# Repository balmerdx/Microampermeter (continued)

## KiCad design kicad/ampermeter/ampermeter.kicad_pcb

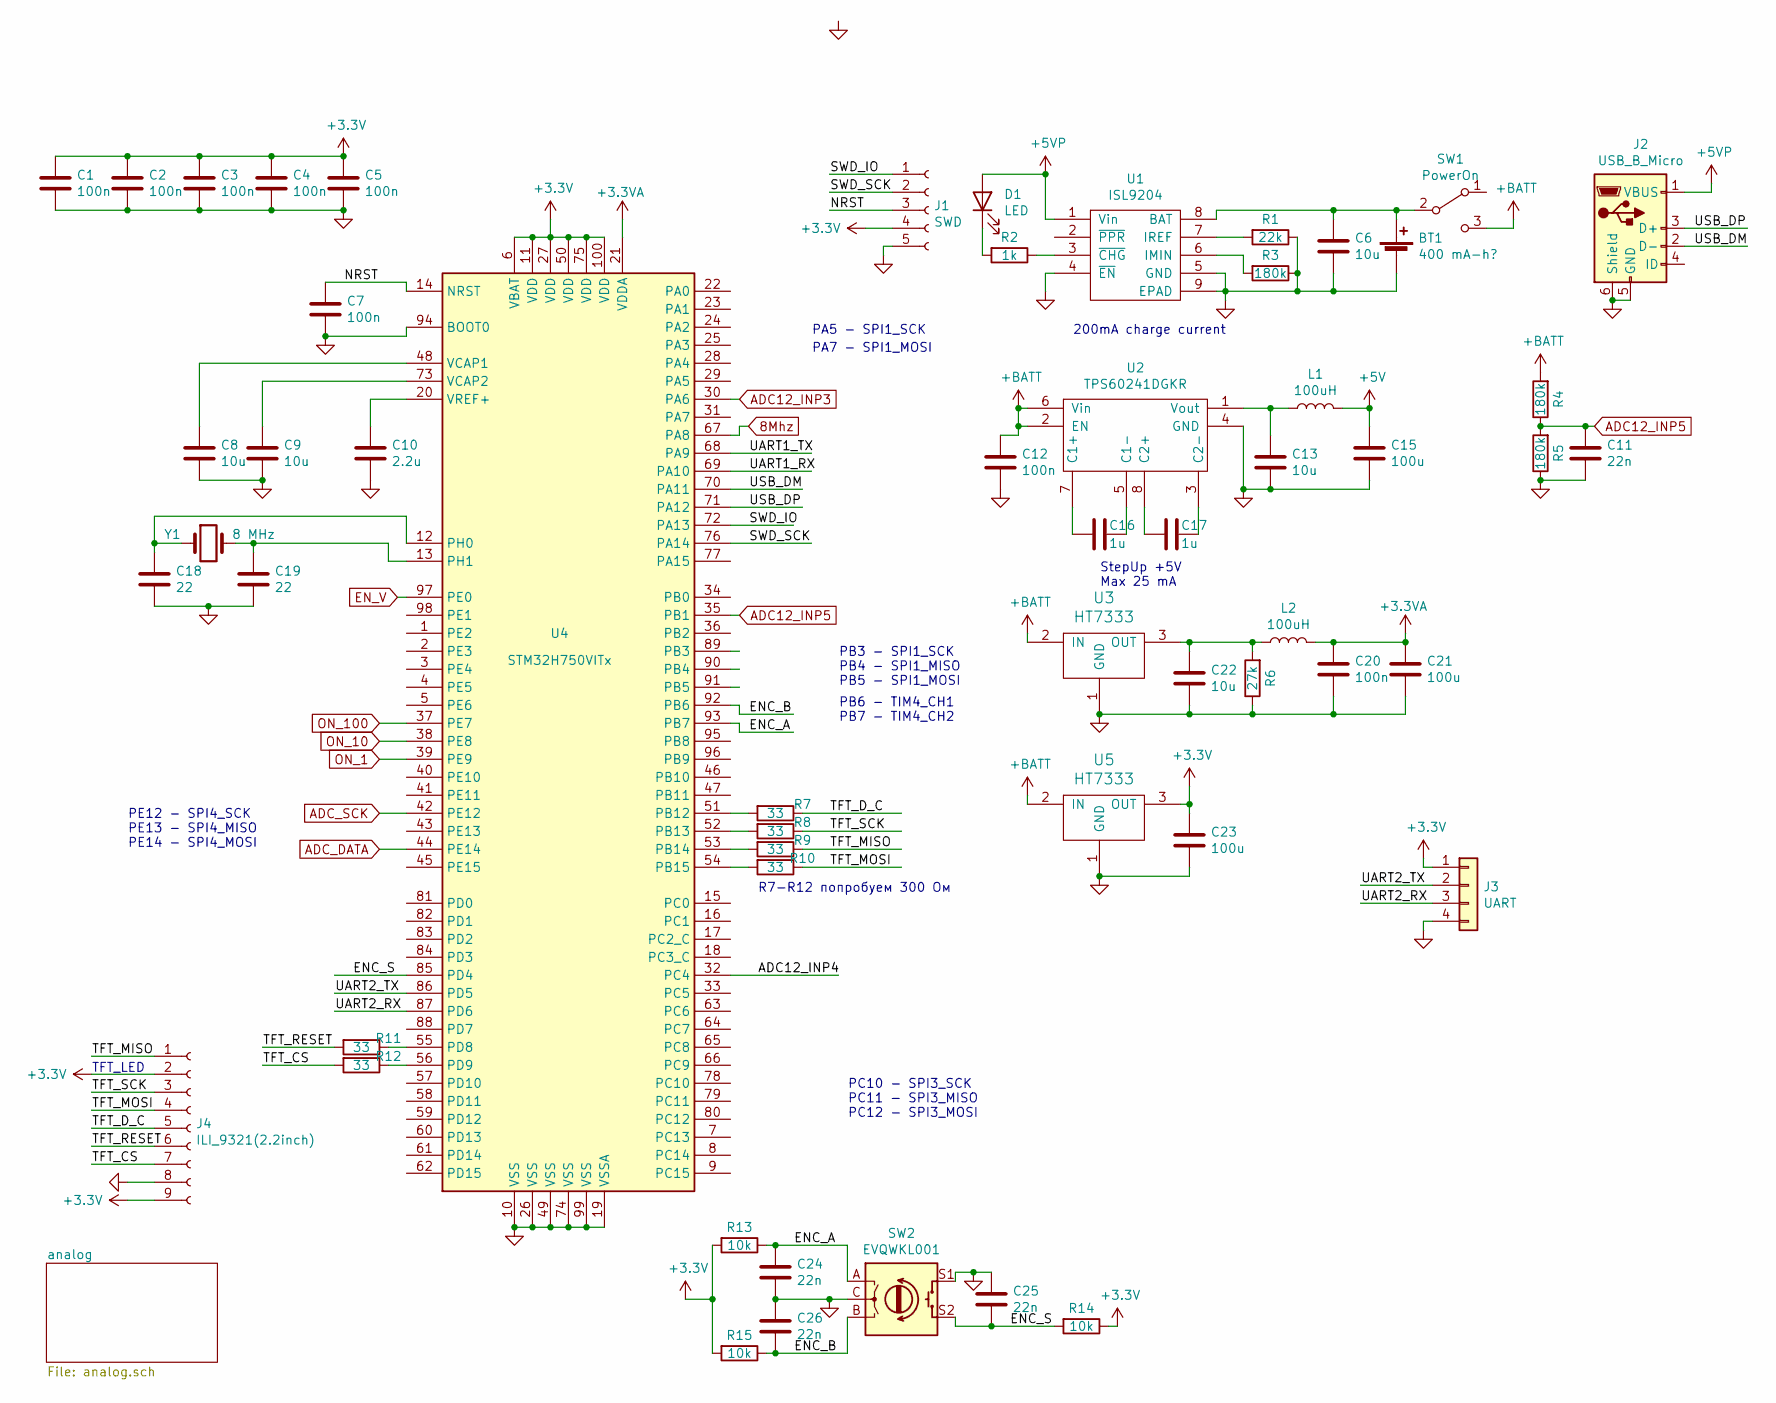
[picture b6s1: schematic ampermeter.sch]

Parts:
BT1: 400 mA-h?; PinSocket_1x02_P2.54mm_Vertical
C1, C2, C3, C4, C5, C7, C12, C20: 100n; C_0603_1608Metric
C6, C8, C9, C13, C22: 10u; C_1206_3216Metric
C10: 2.2u; C_0805_2012Metric
C11, C24, C25, C26: 22n; C_0603_1608Metric
C15, C21, C23: 100u; C_1206_3216Metric
C16, C17: 1u; C_0805_2012Metric
C18, C19: 22; C_0603_1608Metric
D1: LED; LED_0805_2012Metric_Pad1.15x1.40mm_HandSolder
J1: SWD; PinSocket_1x05_P1.27mm_Vertical
J2: USB_B_Micro; USB_Micro-B_Molex-105017-0001
J3: UART; PinHeader_1x04_P2.54mm_Horizontal
J4: ILI_9321(2.2inch)
L1, L2: 100uH; L_Axial_L5.3mm_D2.2mm_P7.62mm_Horizontal_Vishay_IM-1
R1: 22k; R_0603_1608Metric
R2: 1k; R_0603_1608Metric
R3, R4, R5: 180k; R_0603_1608Metric
R6: 27k; R_0603_1608Metric
R7, R8, R9, R10, R11, R12: 33; R_0603_1608Metric
R13, R14, R15: 10k; R_0603_1608Metric
SW1: PowerOn; SW_Angled_with_GND
SW2: EVQWKL001; Encoder_EVQWK4
U1: ISL9204; DFN-8-1EP_3x2mm_P0.5mm_EP1.75x1.65mm
U2: TPS60241DGKR; TSSOP-8_3x3mm_P0.65mm
U3, U5: HT7333; SOT-89-3
U4: STM32H750VITx; LQFP-100_14x14mm_P0.5mm
Y1: 8 MHz; Crystal_SMD_5032-2Pin_5.0x3.2mm

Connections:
8Mhz: U4.67 (PA8); also elsewhere on the board
+3.3VA: C20.1, C21.1, L2.2, U4.21 (VDDA)
+3V3: C1.1, C2.1, C3.1, C4.1, C5.1, C23.1, J1.4, J3.1, J4.2, J4.9, R13.2, R14.1, R15.2, U4.6 (VBAT), U4.11 (VDD), U4.27 (VDD), U4.50 (VDD), U4.75 (VDD), U4.100 (VDD), U5.3 (OUT)
+5V: C15.1, L1.2; also elsewhere on the board
+5VP: D1.2 (A), J2.1 (VBUS), U1.1 (Vin)
+BATT: C12.1, R4.2, SW1.3 (C), U2.2 (EN), U2.6 (Vin), U3.2 (IN), U5.2 (IN); also elsewhere on the board
/ADC12_INP4: U4.32 (PC4)
/ENC_A: C24.1, R13.1, SW2.A, U4.93 (PB7)
/ENC_B: C26.2, R15.1, SW2.B, U4.92 (PB6)
/ENC_S: C25.2, R14.2, SW2.S2, U4.85 (PD4)
/NRST: C7.1, J1.3, U4.14 (NRST)
/SWD_IO: J1.1, U4.72 (PA13)
/SWD_SCK: J1.2, U4.76 (PA14)
/TFT_CS: J4.7, R12.2
/TFT_D_C: J4.5, R7.1
/TFT_MISO: J4.1, R9.1
/TFT_MOSI: J4.4, R10.1
/TFT_RESET: J4.6, R11.2
/TFT_SCK: J4.3, R8.1
/UART1_RX: U4.69 (PA10)
/UART1_TX: U4.68 (PA9)
/UART2_RX: J3.3, U4.87 (PD6)
/UART2_TX: J3.2, U4.86 (PD5)
/USB_DM: J2.2 (D-), U4.70 (PA11)
/USB_DP: J2.3 (D+), U4.71 (PA12)
ADC12_INP3: U4.30 (PA6); also elsewhere on the board
ADC12_INP5: C11.1, R4.1, R5.2, U4.35 (PB1)
ADC_DATA: U4.44 (PE14); also elsewhere on the board
ADC_SCK: U4.42 (PE12); also elsewhere on the board
EN_V: U4.97 (PE0); also elsewhere on the board
GND: BT1.2 (-), C1.2, C2.2, C3.2, C4.2, C5.2, C6.2, C7.2, C8.2, C9.2, C10.2, C11.2, C12.2, C13.2, C15.2, C18.2, C19.2, C20.2, C21.2, C22.2, C23.2, C24.2, C25.1, C26.1, J1.5, J2.5 (GND), J2.6 (Shield), J3.4, J4.8, R1.1, R3.1, R5.1, R6.1, SW2.C, SW2.GND, SW2.PAD, SW2.S1, U1.4 (~EN), U1.5 (GND), U1.9 (EPAD), U2.4 (GND), U3.1 (GND), U4.10 (VSS), U4.19 (VSSA), U4.26 (VSS), U4.49 (VSS), U4.74 (VSS), U4.94 (BOOT0), U4.99 (VSS), U5.1 (GND); also elsewhere on the board
unnamed: BT1.1 (+), C6.1, SW1.2 (B), U1.8 (BAT)
unnamed: C8.1, U4.48 (VCAP1)
unnamed: C9.1, U4.73 (VCAP2)
unnamed: C10.1, U4.20 (VREF+)
unnamed: C13.1, L1.1, U2.1 (Vout)
unnamed: C16.1, U2.5 (C1-)
unnamed: C16.2, U2.7 (C1+)
unnamed: C17.1, U2.3 (C2-)
unnamed: C17.2, U2.8 (C2+)
unnamed: C18.1, U4.12 (PH0), Y1.1
unnamed: C19.1, U4.13 (PH1), Y1.2
unnamed: C22.1, L2.1, R6.2, U3.3 (OUT)
unnamed: D1.1 (K), R2.2
unnamed: R1.2, U1.7 (IREF)
unnamed: R2.1, U1.3 (~CHG)
unnamed: R3.2, U1.6 (IMIN)
unnamed: R7.2, U4.51 (PB12)
unnamed: R8.2, U4.52 (PB13)
unnamed: R9.2, U4.53 (PB14)
unnamed: R10.2, U4.54 (PB15)
unnamed: R11.1, U4.55 (PD8)
unnamed: R12.1, U4.56 (PD9)
ON_1: U4.39 (PE9); also elsewhere on the board
ON_10: U4.38 (PE8); also elsewhere on the board
ON_100: U4.37 (PE7); also elsewhere on the board

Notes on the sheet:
200mA charge current
TFT_LED
StepUp +5V Max 25 mA
PB3 - SPI1_SCK PB4 - SPI1_MISO PB5 - SPI1_MOSI
PC10 - SPI3_SCK PC11 - SPI3_MISO PC12 - SPI3_MOSI
PB6 - TIM4_CH1 PB7 - TIM4_CH2
PA5 - SPI1_SCK
PA7 - SPI1_MOSI
PE12 - SPI4_SCK PE13 - SPI4_MISO PE14 - SPI4_MOSI
R7-R12 попробуем 300 Ом

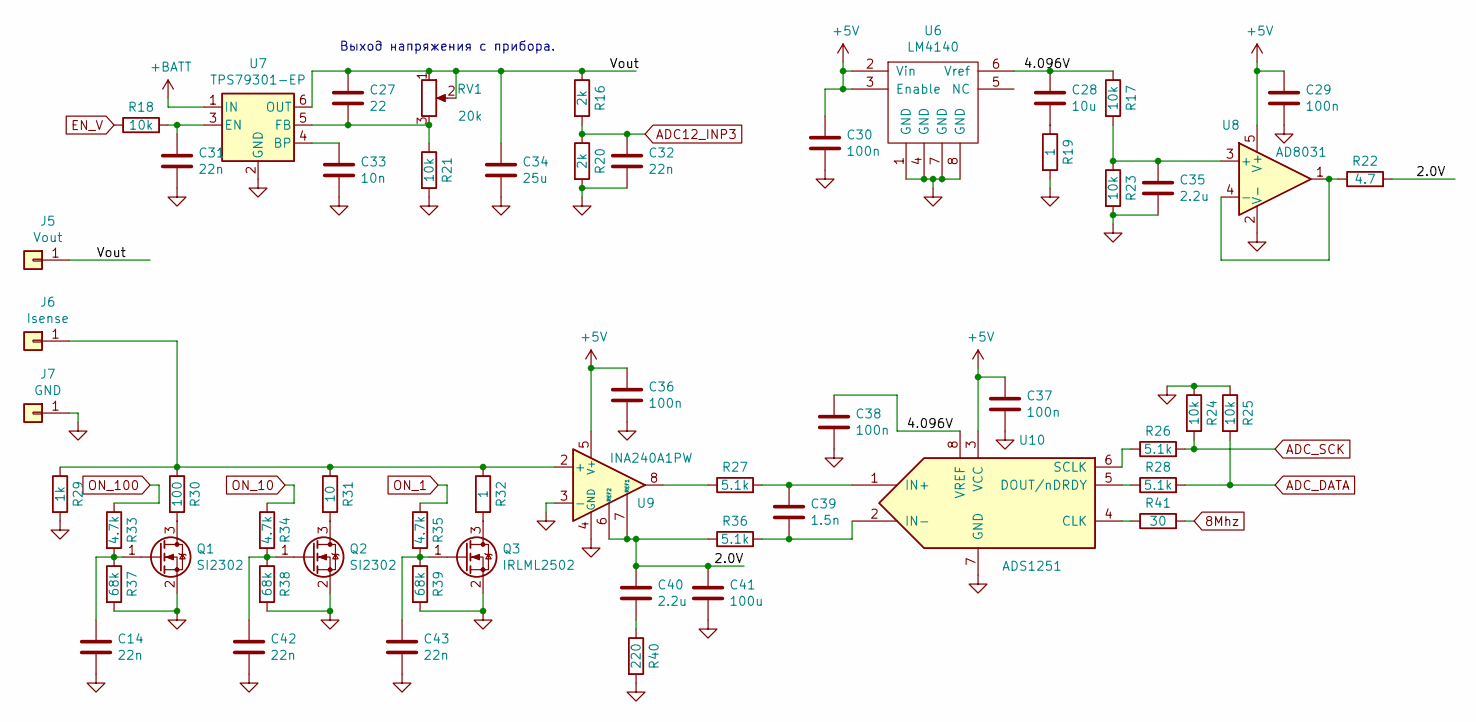
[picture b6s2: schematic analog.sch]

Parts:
C14, C31, C32, C42, C43: 22n; C_0603_1608Metric
C27: 22; C_0603_1608Metric
C28: 10u; C_1206_3216Metric
C29, C30, C36, C37, C38: 100n; C_0603_1608Metric
C33: 10n; C_0603_1608Metric
C34: 25u; C_1206_3216Metric
C35, C40: 2.2u; C_0805_2012Metric
C39: 1.5n; C_1206_3216Metric
C41: 100u; C_1206_3216Metric
J5: Vout; Pin_D1.0mm_L10.0mm_LooseFit
J6: Isense; Pin_D1.0mm_L10.0mm_LooseFit
J7: GND; Pin_D1.0mm_L10.0mm_LooseFit
Q1, Q2: SI2302; SOT-23
Q3: IRLML2502; SOT-23
R16, R20: 2k; R_0603_1608Metric
R17, R18, R21, R23, R24, R25: 10k; R_0603_1608Metric
R19: 1; R_0603_1608Metric
R22: 4.7; R_0603_1608Metric
R26, R27, R28, R36: 5.1k; R_0603_1608Metric
R29: 1k; R_0603_1608Metric
R30: 100; R_0603_1608Metric
R31: 10; R_0603_1608Metric
R32: 1; R_0805_2012Metric
R33, R34, R35: 4.7k; R_0603_1608Metric
R37, R38, R39: 68k; R_0603_1608Metric
R40: 220; R_0603_1608Metric
R41: 30; R_0603_1608Metric
RV1: 20k; Potentiometer_10mm
U6: LM4140; SO-8_3.9x4.9mm_P1.27mm
U7: TPS79301-EP; SOT-23-6
U8: AD8031; SOT-23-5
U9: INA240A1PW; TSSOP-8_4.4x3mm_P0.65mm
U10: ADS1251; SOIC-8_3.9x4.9mm_P1.27mm

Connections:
8Mhz: R41.2; also elsewhere on the board
+5V: C29.1, C30.1, C36.1, C37.1, U6.2 (Vin), U6.3 (Enable), U8.5 (V+), U9.5 (V+), U10.3 (VCC); also elsewhere on the board
+BATT: U7.1 (IN); also elsewhere on the board
/analog/2.0V: C40.1, C41.1, R22.2, R36.1, U9.6 (REF2), U9.7 (REF1)
/analog/4.096V: C28.1, C38.1, R17.1, U6.6 (Vref), U10.8 (VREF)
/analog/Vout: C27.1, C34.1, J5.1, R16.1, RV1.1, RV1.2, U7.6 (OUT)
ADC12_INP3: C32.1, R16.2, R20.1; also elsewhere on the board
ADC_DATA: R25.2, R28.2; also elsewhere on the board
ADC_SCK: R24.2, R26.2; also elsewhere on the board
EN_V: R18.1; also elsewhere on the board
GND: C14.2, C29.2, C30.2, C31.2, C32.2, C33.2, C34.2, C35.2, C36.2, C37.2, C38.2, C41.2, C42.2, C43.2, J7.1, Q1.2 (S), Q2.2 (S), Q3.2 (S), R19.2, R20.2, R21.2, R23.2, R24.1, R25.1, R29.2, R37.2, R38.2, R39.2, R40.2, U6.1 (GND), U6.4 (GND), U6.7 (GND), U6.8 (GND), U7.2 (GND), U8.2 (V-), U9.1 (GND), U9.3 (-), U9.4 (GND), U10.7 (GND); also elsewhere on the board
unnamed: C14.1, Q1.1 (G), R33.2, R37.1
unnamed: C27.2, R21.1, RV1.3, U7.5 (FB)
unnamed: C28.2, R19.1
unnamed: C31.1, R18.2, U7.3 (EN)
unnamed: C33.1, U7.4 (BP)
unnamed: C35.1, R17.2, R23.1, U8.3 (+)
unnamed: C39.1, R27.2, U10.1 (IN+)
unnamed: C39.2, R36.2, U10.2 (IN-)
unnamed: C40.2, R40.1
unnamed: C42.1, Q2.1 (G), R34.2, R38.1
unnamed: C43.1, Q3.1 (G), R35.2, R39.1
unnamed: J6.1, R29.1, R30.1, R31.1, R32.1, U9.2 (+)
unnamed: Q1.3 (D), R30.2
unnamed: Q2.3 (D), R31.2
unnamed: Q3.3 (D), R32.2
unnamed: R22.1, U8.1, U8.4 (-)
unnamed: R26.1, U10.6 (SCLK)
unnamed: R27.1, U9.8
unnamed: R28.1, U10.5 (DOUT/nDRDY)
unnamed: R41.1, U10.4 (CLK)
ON_1: R35.1; also elsewhere on the board
ON_10: R34.1; also elsewhere on the board
ON_100: R33.1; also elsewhere on the board

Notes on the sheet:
Выход напряжения с прибора.

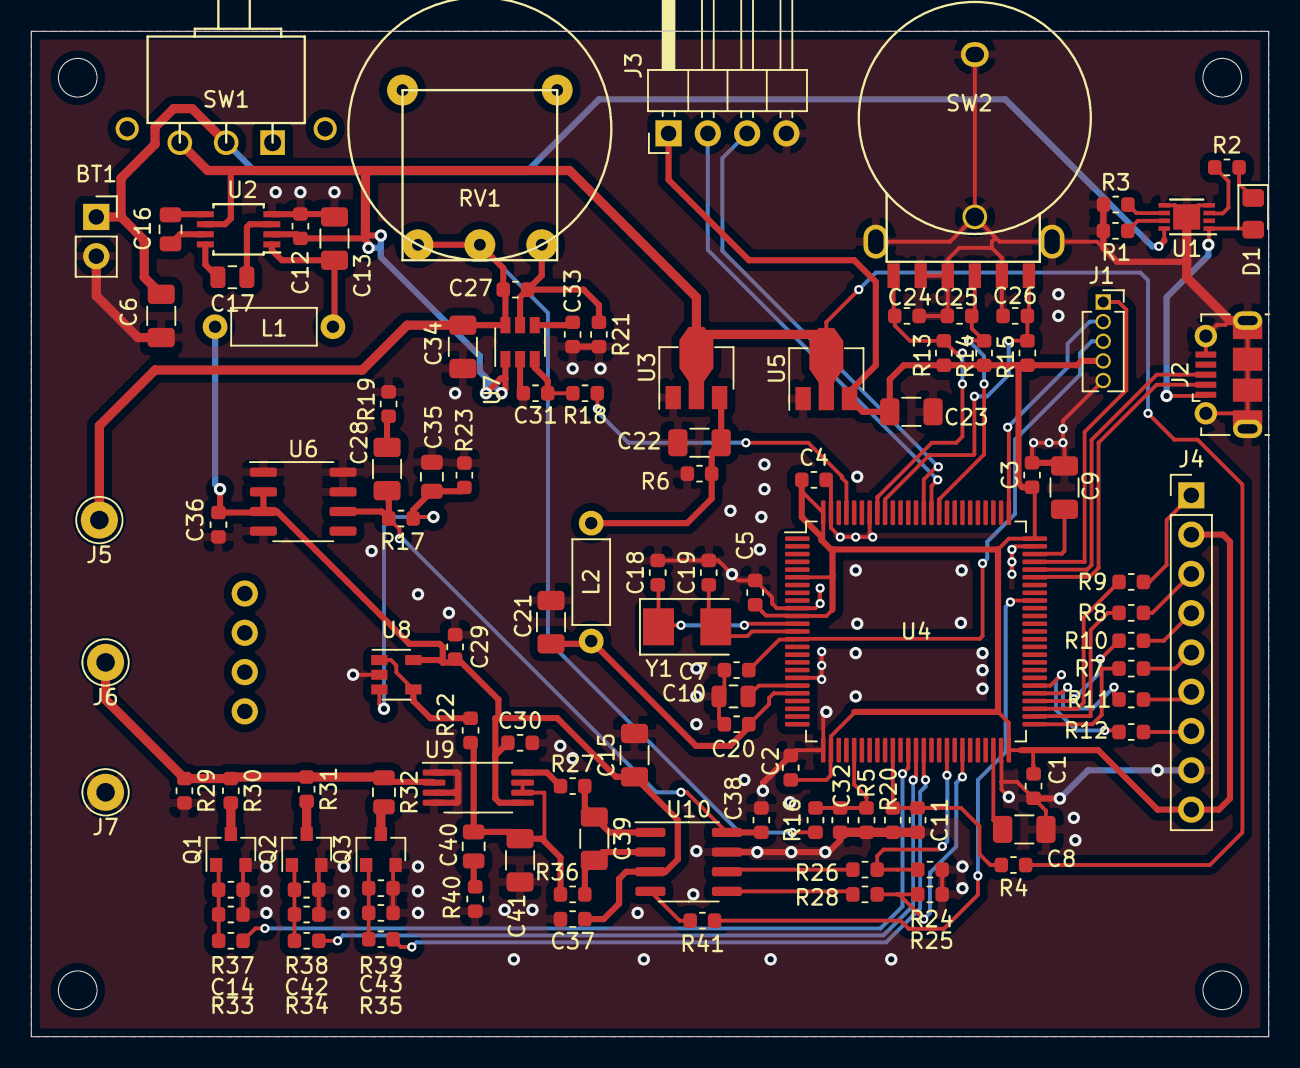
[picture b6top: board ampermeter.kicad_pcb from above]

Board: 2 copper layers, 80.0 x 65.0 mm, 112 parts (0 on the bottom side), 76 nets.

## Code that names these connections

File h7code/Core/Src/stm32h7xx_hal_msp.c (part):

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    __HAL_RCC_GPIOC_CLK_ENABLE();
    __HAL_RCC_MDMA_CLK_ENABLE();
    /**QUADSPI GPIO Configuration
    PB2     ------> QUADSPI_CLK
    PE7     ------> QUADSPI_BK2_IO0
    PE8     ------> QUADSPI_BK2_IO1
    PE9     ------> QUADSPI_BK2_IO2
    PE10     ------> QUADSPI_BK2_IO3
    PC11     ------> QUADSPI_BK2_NCS
    */
    GPIO_InitStruct.Pin = GPIO_PIN_2;
    GPIO_InitStruct.Mode = GPIO_MODE_AF_PP;
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    __HAL_RCC_QSPI_CLK_DISABLE();

    /**QUADSPI GPIO Configuration
    PB2     ------> QUADSPI_CLK
    PE7     ------> QUADSPI_BK2_IO0
    PE8     ------> QUADSPI_BK2_IO1
    PE9     ------> QUADSPI_BK2_IO2
    PE10     ------> QUADSPI_BK2_IO3
    PC11     ------> QUADSPI_BK2_NCS
    */
    HAL_GPIO_DeInit(GPIOB, GPIO_PIN_2);

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    SAI1_client ++;

    /**SAI1_A_Block_A GPIO Configuration
    PE2     ------> SAI1_MCLK_A
    PE4     ------> SAI1_FS_A
    PE5     ------> SAI1_SCK_A
    PE6     ------> SAI1_SD_A
    */
    GPIO_InitStruct.Pin = GPIO_PIN_2|GPIO_PIN_4|GPIO_PIN_5|GPIO_PIN_6;
    GPIO_InitStruct.Mode = GPIO_MODE_AF_PP;
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        }

        /**SAI1_A_Block_A GPIO Configuration
        PE2     ------> SAI1_MCLK_A
        PE4     ------> SAI1_FS_A
        PE5     ------> SAI1_SCK_A
        PE6     ------> SAI1_SD_A
        */
        HAL_GPIO_DeInit(GPIOE, GPIO_PIN_2|GPIO_PIN_4|GPIO_PIN_5|GPIO_PIN_6);

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
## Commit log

2020-10-07 - kicad schematic
2020-10-09 - изначальный коммит кода
2020-10-09 - ADC заработало в простейшем режиме
2020-12-20 - изменения скопом, за огромный промежуток времени
2021-01-14 - новая графическая библиотека и более-менее работающий QSPI flash
2021-01-14 - работает, но со скоростью только 7 МБ/сек
2021-01-14 - QSPI MDMA 28 МБ/сек
2021-01-14 - проверили чтение запись всех 8 МБ памяти
2021-01-16 - мелкие изменения перед попыткой запустить SAI
2021-01-17 - работающий HAL_SAI_Receive_DMA причем похоже в правильных частотах
2021-01-17 - HAL_SAI_Receive_DMA не работает, HAL_SAI_Receive - выдаёт фигню
2021-01-17 - что-то выводит, но DMA не работает
2021-01-18 - получили какие-то разумные цифры с аналоговой части
2021-01-18 - начинаем разносить код в разные файлы
2021-01-19 - слили данные на компьютер
2021-01-19 - program_release.bin был 650 МБ, добавили (NOLOAD) и стало 45 кб
    - корректно работает с отрицательными значениями ADC
2021-01-23 - попробовали компилировать clang
    - уточнили временно корректировку
2021-01-23 - .ignore
2021-01-25 - передаются корректные данные на usb
    - множество мелких изменений
2021-01-27 - SendAdcCurrentNanoampers r shift & HAL_DMA_IRQHandlerSai
    HAL_DMA_IRQHandlerSai - укороченный вариант, чтобы побыстрее работало прерывание
    SendAdcCurrentNanoampers учитывает, что при переключении у нас есть большая задержка ADC (из-за фильтра встроенного в неё)
2021-01-27 - захардкодили DMA1_Stream0
2021-01-31 - небольшой рефактор, для того, чтобы было более удобно ввести задержку R
2021-01-31 - samples_r_buffer даёт требуемую задержку
2021-02-02 - считаем процент времени проведённый в прерывании
2021-02-02 - invalid samples в самом начале
2021-02-03 - вынес подсчет среднего в отдельный файл
2021-02-05 - вынесли начальный интерфейс в отдельный файл
2021-02-05 - более-менее пристойный вывод на экран
2021-02-06 - очень большой фонт, показываем % времени проведённого в прерывании
2021-02-06 - показываем минимальный/максимальный ток
2021-02-06 - фильтруем верхние частоты x16 для min/max
2021-02-07 - отделили подсчёт тока в отдельную функцию
2021-02-07 - фильтруем ток, а не adc_I
2021-02-07 - фильтруем с разной частотой, меню по этому поводу
2021-02-07 - переключение line2, исправили расчёт сопротивления
2021-02-11 - попробовали писать во flash за пределы первой страницы (неудачно)
    - запаяли qspi flash и заставили её работать в spi режиме
2021-02-11 - vbat напряжение на процессоре (но неточное)
2021-02-11 - battery full/empty
2021-02-11 - flash вроде работает корректно
2021-02-12 - calibration zero рабочий, calibration hard только начали
2021-02-13 - корректировка коэффициента усиления канала тока
2021-02-13 - настройки сопротивлений разных диапазонов
2021-02-13 - settings permanent запоминаются
    можно посмотреть на корректировочные коэффициенты
2021-02-14 - запоминаем настройки line2 и FilterX
2021-02-14 - начинаем делать гистограмму
2021-02-14 - начали заполнять цифрами вертикальную ось
2021-02-15 - шкала справа корректно обновляется
2021-02-16 - таки увидели реальную гистограмму
2021-02-18 - время суммирования гистограммы. Выбор microampermetr/histogramm
2021-03-03 - коробочка готовая (правда дырки сверлили под щупы)
2021-03-13 - отдельно калибруем offset voltage и offset current
    - кое-как завершил гистограммы
2021-03-14 - путь для тока и напряжения теперь более единообразен
2021-03-15 - проверенный циклический буфер
    - добавили пустую сцену для осциллоскопа
2021-03-20 - начали писать данные в огромный буффер
    - заодно исправили косяки при переключении диапазонов и отрицательном токе
2021-03-20 - окошко как в осциллографе прикрутили, 80 FPS отрисовывает
2021-03-21 - увидели первый график
2021-03-21 - scale current & time работают в меню
2021-03-21 - на заднем фоне рисуем min/max текущего значения
2021-03-23 - offset time работает в осциллографе
2021-03-26 - учитываем случай, когда линия одновременно выходит за границы сверху и снизу
2021-03-26 - menu trigger level
2021-03-26 - нормальный график в случае, если данных меньше, чем пикселей
2021-03-28 - trigger level rising/falling
2021-03-28 - trigger started/completed теперь цветом отображается
    - first_sample_offset теперь не изменяется после того, как триггер сработал
    - progress bar теперь показывает сколько осталось до окончания сэмплирования, либо текущий offset на графике
2021-03-29 - теперь график единоразово обновляется в момент, когда сработал триггер и уже достаточно данных, чтобы на экране нарисовать
2021-03-29 - батарейку нарисовать в конце осциллографа
    - добавить Bandwidth в меню осциллографа
2021-03-29 - запись настроек отложенная
    - scene About
2021-03-30 - корректно определяем circle_buffer.first_sample_offset при срабатывании триггера
2021-04-15 - sch info text
2023-02-03 add microampermeter picture
